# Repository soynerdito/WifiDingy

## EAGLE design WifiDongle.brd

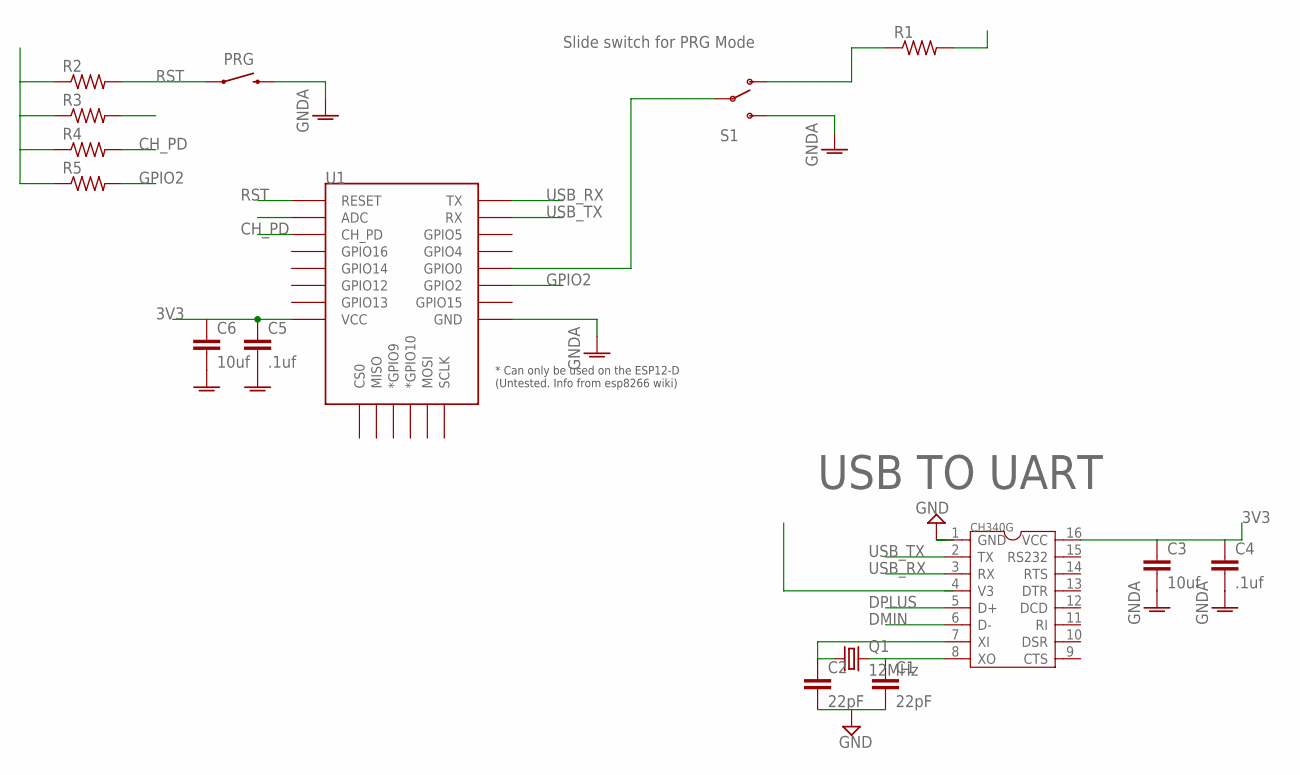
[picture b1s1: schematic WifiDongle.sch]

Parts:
C1, C2: 22pF; 0603-CAP
C3, C6: 10uf; 0603-CAP
C4, C5: .1uf; 0603-CAP
CH340G: CH340GCH340G; SOP-16
PRG: SWITCH-MOMENTARY-2SMD-REDUNDANT; TACTILE-SWITCH-SMD
Q1: 12MHz; HC49U70
R1, R2, R3, R4, R5: R-US_R0603; R0603
S1: SWITCH-SPDT-SMD-A; SWITCH-SPST-SMD-A
U1: ESP12ESMD; ESP12E-SMD

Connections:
3V3: C3.1, C4.1, C5.1, C6.1, CH340G.16 (VCC), U1.VCC
CH_PD: R4.2, U1.CH_PD
DMIN: CH340G.6 (D-)
DPLUS: CH340G.5 (D+)
GND: C1.2, C2.2, CH340G.1 (GND)
GNDA: C3.2, C4.2, C5.2, C6.2, PRG.3 (2), PRG.4 (2), S1.3 (S), U1.GND
GPIO2: R5.2, U1.GPIO2
unnamed: S1.2, U1.GPIO0
unnamed: R1.1, S1.1 (O)
unnamed: R2.1, R3.1, R4.1, R5.1
RST: PRG.1, PRG.2 (1), R2.2, U1.RESET
USB_RX: CH340G.3 (RX), U1.TXD0 (TX)
USB_TX: CH340G.2 (TX), U1.RXD0 (RX)
XI: C2.1, CH340G.7 (XI), Q1.1
XO: C1.1, CH340G.8 (XO), Q1.2

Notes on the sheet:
USB TO UART
Slide switch for PRG Mode

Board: 2 copper layers, 16 parts (0 on the bottom side), 13 nets, no tracks yet.

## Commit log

2016-11-11 Initial commit, work in progress

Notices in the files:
parts and their libraries:
SparkFun-Capacitors: Licensing: Creative Commons ShareAlike 4.0 International - https://creativecommons.org/licenses/by-sa/4.0
